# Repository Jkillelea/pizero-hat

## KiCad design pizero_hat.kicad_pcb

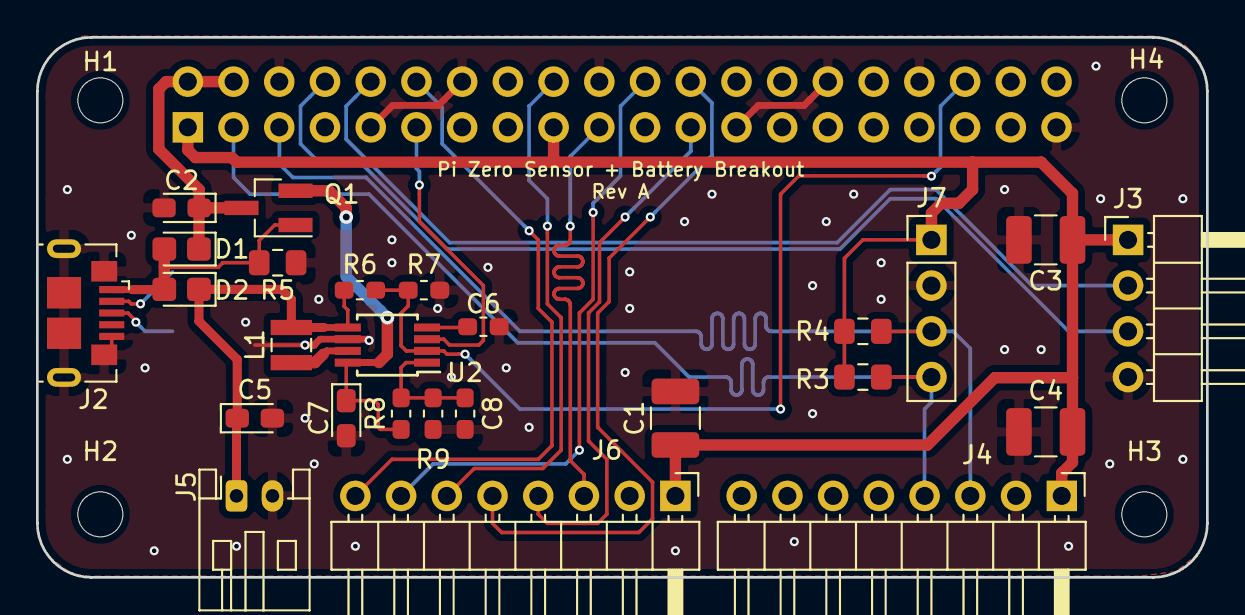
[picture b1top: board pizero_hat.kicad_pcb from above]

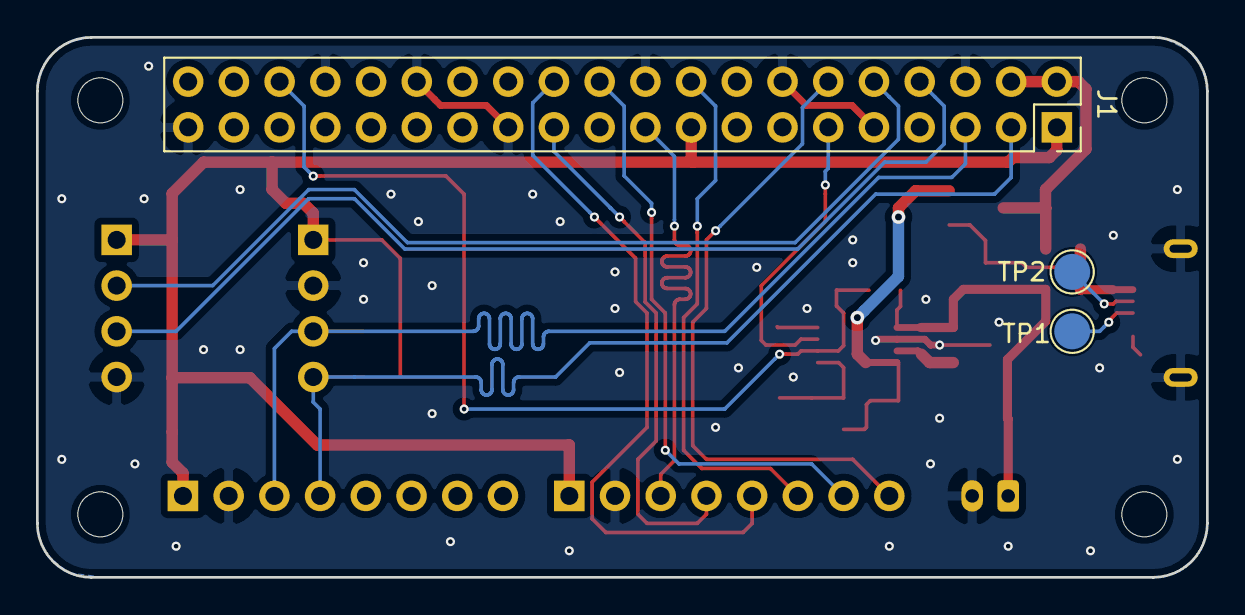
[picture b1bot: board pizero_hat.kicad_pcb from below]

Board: 2 copper layers, 65.0 x 30.0 mm, 33 parts (3 on the bottom side), 23 nets.

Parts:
C1, C3, C4: 0.1uF; C_1210_3225Metric_Pad1.42x2.65mm_HandSolder
C2: 10uF; CP_EIA-2012-12_Kemet-R_Pad1.30x1.05mm_HandSolder
C5, C7: 22uF; CP_EIA-2012-12_Kemet-R_Pad1.30x1.05mm_HandSolder
C6: 200nF; C_0603_1608Metric_Pad1.05x0.95mm_HandSolder
C8: 10pF; C_0603_1608Metric_Pad1.05x0.95mm_HandSolder
D1, D2: D_Schottky; D_0805_2012Metric_Castellated
H1, H2, H3, H4: MountingHole; MountingHole_2.5mm
J1: Raspberry_Pi_2_3; PinSocket_2x20_P2.54mm_Vertical
J2: USB_B_Micro; USB_Micro-B_GCT_USB3076-30-A
J3: NEO_6M; PinHeader_1x04_P2.54mm_Horizontal
J4: MPU6050; PinHeader_1x08_P2.54mm_Horizontal
J5: JST PH; JST_PH_S2B-PH-K_1x02_P2.00mm_Horizontal
J6: Conn_01x08_Female; PinHeader_1x08_P2.54mm_Horizontal
J7: SSD1306; PinHeader_1x04_P2.54mm_Vertical
L1: 10uH; L_Wuerth_MAPI-2512
Q1: Si2333CDS; SOT-23_Handsoldering
R3, R4, R5: 10k; R_0805_2012Metric_Pad1.15x1.40mm_HandSolder
R6: 56k; R_0603_1608Metric_Pad1.05x0.95mm_HandSolder
R7: 47k; R_0603_1608Metric_Pad1.05x0.95mm_HandSolder
R8: 383k; R_0603_1608Metric_Pad1.05x0.95mm_HandSolder
R9: 120k; R_0603_1608Metric_Pad1.05x0.95mm_HandSolder
TP1, TP2: TestPoint; TestPoint_Pad_D2.0mm
U2: NCP1421; MSOP-8_3x3mm_P0.65mm

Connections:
+3V3: C1.1, C3.1, C4.1, J1.1, J1.17, J3.1, J4.1, J6.1, J7.1, R3.1, R4.1
+5V: C2.1, D1.1, J1.2, J1.4, Q1.3
+BATT: C5.1, D2.1, J5.1, L1.1, R6.1, U2.5
/Boost Converter/LBI_EN: J1.36, R6.2, R7.1, U2.2
/Boost Converter/LBO: J1.11, U2.3
/DISP_BL: J1.12, J6.8
/DISP_CLK: J1.23, J6.4
/DISP_CS: J1.24, J6.5
/DISP_DC: J1.18, J6.6
/DISP_DIN: J1.19, J6.3
/DISP_RST: J1.22, J6.7
/Vbus: D1.2, D2.2, J2.1, Q1.1, R5.1
D+: J2.3, TP1.1
D-: J2.2, TP2.1
GND: C1.2, C2.2, C3.2, C4.2, C5.2, C6.1, C7.2, C8.1, J1.6, J1.9, J1.14, J1.20, J1.25, J1.30, J1.34, J1.39, J2.5, J2.6, J3.4, J4.2, J5.2, J6.2, J7.2, R5.2, R7.2, R9.2, U2.6
unnamed: C6.2, U2.4
unnamed: C8.2, R8.2, R9.1, U2.1
unnamed: L1.2, U2.7
SCL: J1.5, J4.3, J7.3, R4.2
SDA: J1.3, J4.4, J7.4, R3.2
UART_RX: J1.10, J3.2
UART_TX: J1.8, J3.3
Vboost: C7.1, Q1.2, R8.1, U2.8

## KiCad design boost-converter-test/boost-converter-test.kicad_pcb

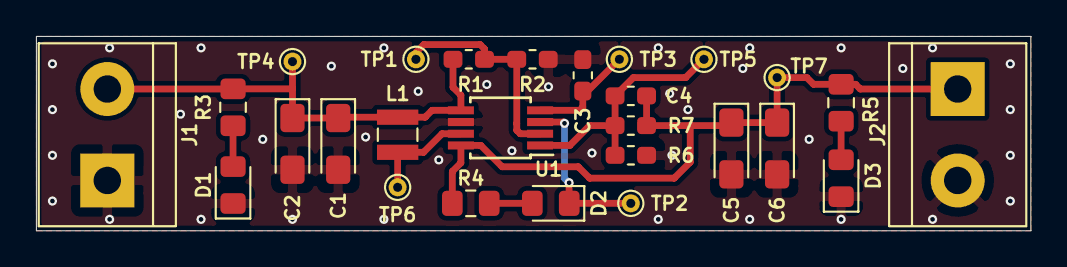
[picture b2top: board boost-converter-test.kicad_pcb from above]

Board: 2 copper layers, 55.2 x 10.8 mm, 27 parts (0 on the bottom side), 11 nets.

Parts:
C1, C2, C5, C6: 10uF; CP_EIA-3216-18_Kemet-A_Pad1.58x1.35mm_HandSolder
C3: 200nF; C_0603_1608Metric_Pad1.05x0.95mm_HandSolder
C4: 10pF; C_0603_1608Metric_Pad1.05x0.95mm_HandSolder
D1, D2, D3: LED G; LED_0805_2012Metric_Pad1.15x1.40mm_HandSolder
J1, J2: Screw_Terminal_01x02; TerminalBlock_bornier-2_P5.08mm
L1: 10uH; L_Wuerth_MAPI-2512
R1: 360k; R_0603_1608Metric_Pad1.05x0.95mm_HandSolder
R2: 47k; R_0603_1608Metric_Pad1.05x0.95mm_HandSolder
R3: 180; R_0805_2012Metric_Pad1.15x1.40mm_HandSolder
R4, R5: 330; R_0805_2012Metric_Pad1.15x1.40mm_HandSolder
R6: 120k; R_0603_1608Metric_Pad1.05x0.95mm_HandSolder
R7: 383k; R_0603_1608Metric_Pad1.05x0.95mm_HandSolder
TP1, TP2, TP3, TP4, TP5, TP6, TP7: TestPoint; TestPoint_THTPad_D1.0mm_Drill0.5mm
U1: NCP1421; MSOP-8_3x3mm_P0.65mm

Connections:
+BATT: C1.1, C2.1, J1.2, L1.1, R1.1, R3.1, TP4.1, U1.5
/ncp_fb: C4.1, R6.1, R7.2, TP5.1, U1.1
/ncp_lbi_en: R1.2, R2.1, TP1.1, U1.2
/ncp_lx: L1.2, TP6.1, U1.7
/ncp_ref: C3.2, TP3.1, U1.4
GND: C1.2, C2.2, C3.1, C5.2, C6.2, D1.1, D3.1, J1.1, J2.2, R2.2, R6.2, U1.6
LBO: D2.1, TP2.1, U1.3
unnamed: D1.2, R3.2
unnamed: D2.2, R4.2
unnamed: D3.2, R5.2
Vboost: C4.2, C5.1, C6.1, J2.1, R4.1, R5.1, R7.1, TP7.1, U1.8

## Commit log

2020-05-17 Initial commit. RevA of PCB ordered + test board already built and demonstrated.
2020-05-17 gitignore + 3d models
2020-05-17 Add Rev A note to silkscreen
